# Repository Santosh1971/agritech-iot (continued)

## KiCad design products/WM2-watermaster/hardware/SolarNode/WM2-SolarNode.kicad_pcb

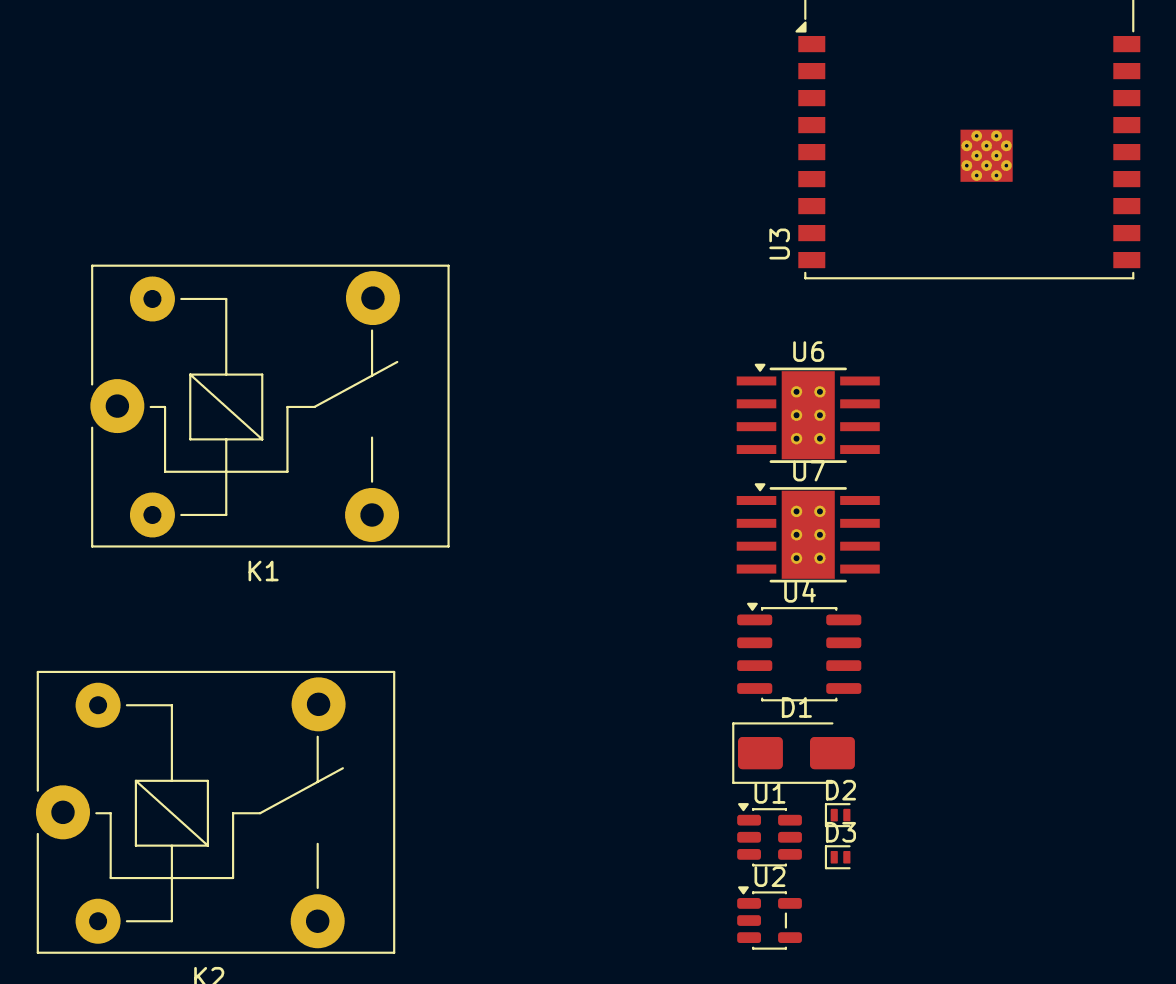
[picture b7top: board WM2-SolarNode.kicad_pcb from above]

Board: 2 copper layers, 11 parts (0 on the bottom side), 12 nets, no tracks yet.

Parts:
D1: SS34 (reverse-polarity); D_SMA
D2: PESD3V3U1UL (D-); D_SOD-882
D3: PESD3V3U1UL (D+); D_SOD-882
K1, K2: SRD-05VDC-SL-C; Relay_SPDT_SANYOU_SRD_Series_Form_C
U1: AP63205WU (fixed 5.0V out); TSOT-23-6
U2: AP2112K-3.3; SOT-23-5
U3: ESP32-C3-WROOM-02
U4: DS1307Z+; SOIC-8_3.9x4.9mm_P1.27mm
U6, U7: DRV8871DDA; Texas_HTSOP-8-1EP_3.9x4.9mm_P1.27mm_EP2.95x4.9mm_Mask2.4x3.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

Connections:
+3V3: U2.5 (VOUT), U3.1 (3V3), U4.8 (VCC)
+5V: K1.2, K2.2, U1.1 (FB), U2.1 (VIN), U2.3 (EN)
+12V: D1.1 (K), U1.2 (EN), U1.3 (IN), U6.5 (VM), U7.5 (VM)
/I2C_SCL: U3.8 (IO9), U4.6 (SCL)
/I2C_SDA: U3.7 (IO8), U4.5 (SDA)
/USB_DM: D2.2 (A), U3.13 (IO18)
/USB_DP: D3.2 (A), U3.14 (IO19)
/VALVE1_IN1: U3.10 (IO10), U6.3 (IN1)
/VALVE1_IN2: U3.11 (IO20/RXD), U6.2 (IN2)
/VALVE2_IN1: U3.12 (IO21/TXD), U7.3 (IN1)
/VALVE2_IN2: U3.16 (IO2), U7.2 (IN2)
GND: D2.1 (K), D3.1 (K), U1.4 (GND), U2.2 (GND), U3.9 (GND), U3.19 (GND), U4.4 (GND), U6.1 (GND), U6.7 (GND), U6.9 (GND), U7.1 (GND), U7.7 (GND), U7.9 (GND)

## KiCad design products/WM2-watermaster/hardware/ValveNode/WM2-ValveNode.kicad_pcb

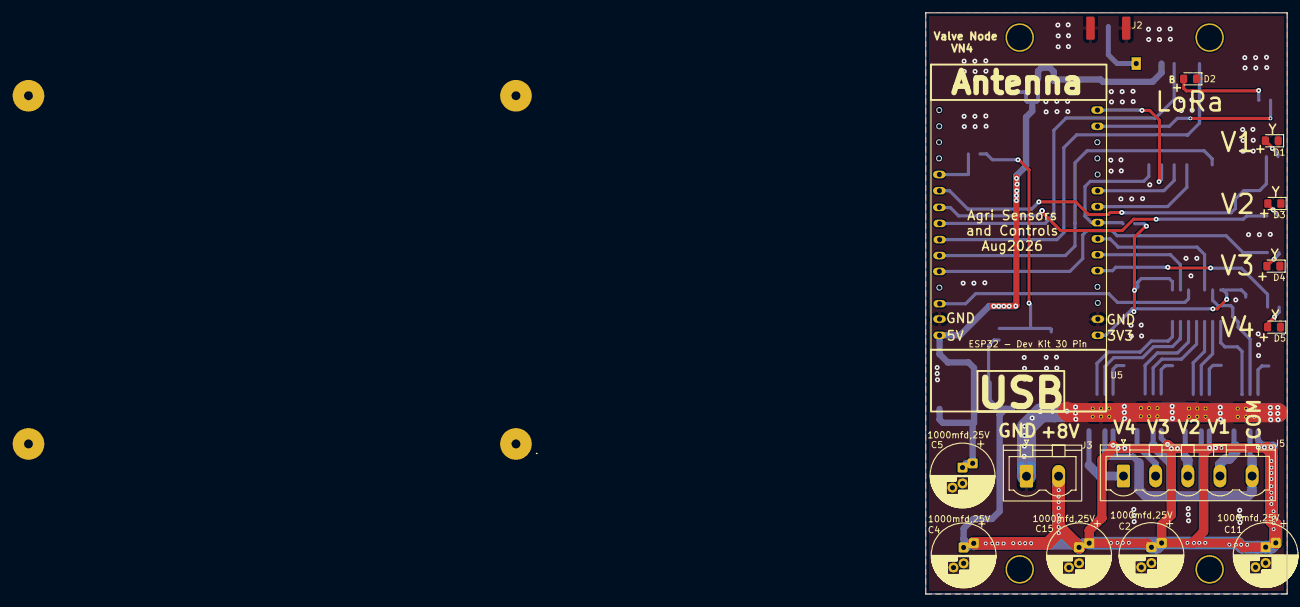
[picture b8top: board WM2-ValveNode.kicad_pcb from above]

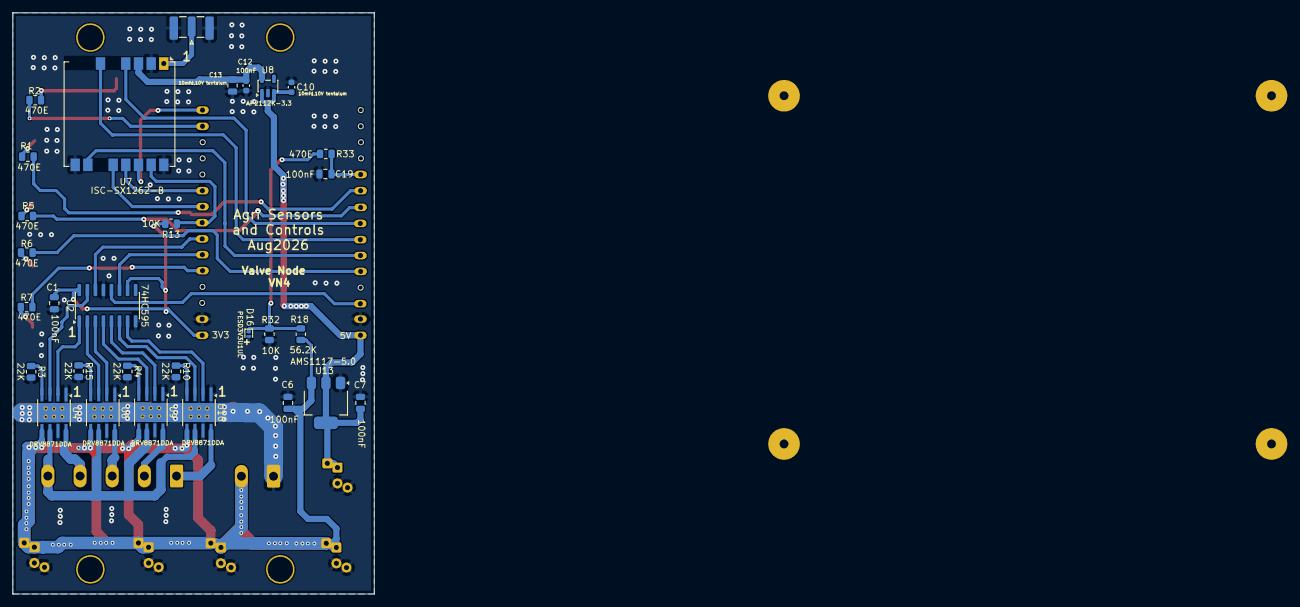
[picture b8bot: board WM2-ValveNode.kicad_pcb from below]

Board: 2 copper layers, 57.1 x 91.8 mm, 45 parts (30 on the bottom side), 45 nets.

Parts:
.: MountingHole; MountingHole_3.2mm_M3
C1, C6, C7, C13, C19: 100nF; C_0805_2012Metric
C2, C4, C5, C11, C15: 1000mfd,25V; CP_Radial_D10.0mm_P2.50mm_P5.00mm
C10, C12: 10mfd,10V tentalum; C_0603_1608Metric
D1: LED_V1_Yellow; LED_0805_2012Metric_Pad1.15x1.40mm_HandSolder
D2: LED_Blue_LoRa; LED_0805_2012Metric_Pad1.15x1.40mm_HandSolder
D3: LED_V2_Yellow; LED_0805_2012Metric_Pad1.15x1.40mm_HandSolder
D4: LED_V3_Yellow; LED_0805_2012Metric_Pad1.15x1.40mm_HandSolder
D5: LED_V4_Yellow; LED_0805_2012Metric_Pad1.15x1.40mm_HandSolder
D16: PESD3V3U1UL; D_SOD-882
H1: MountingHole; MountingHole_3.2mm_M3
J2: Conn_Coaxial_Small; SMA_Samtec_SMA-J-P-H-ST-EM1_EdgeMount
J3: PWR_CONN; PhoenixContact_MSTBVA_2,5_2-G-5,08_1x02_P5.08mm_Vertical
J5: Conn_01x05_Pin; PhoenixContact_MSTBVA_2,5_5-G-5,08_1x05_P5.08mm_Vertical
R1, R2, R5, R6, R7, R33: 470E; R_0805_2012Metric
R3, R4, R10, R15: 22K; R_0805_2012Metric
R13, R32: 10K; R_0805_2012Metric
R18: 56.2K; R_0805_2012Metric
U2: 74HC595; SOIC-16_3.9x9.9mm_P1.27mm
U4, U6, U9, U10: DRV8871DDA; Texas_HTSOP-8-1EP_3.9x4.9mm_P1.27mm_EP2.95x4.9mm_Mask2.4x3.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
U5: ESP32 30 Pin CP2102 Development Board; ESP32-C3-DevKitM-1
U7: ISC-SX1262-B; Ai-Thinker-Ra-01-LoRa
U8: AP2112K-3.3; SOT-23-5
U13: AMS1117-5.0; SOT-223-3_TabPin2

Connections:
+3.3V: C1.1, R13.1, U2.10 (~SRCLR), U2.16 (VCC), U5.1 (3V3_Out)
+3.3VL: C12.1, C13.1, U7.3 (VDD), U8.5 (VOUT)
+5V: C5.1, C7.1, C10.1, U5.30 (VIN/5V_Power_IN), U8.1 (VIN), U8.3 (EN), U13.2 (VO)
+8V: C2.1, C4.1, C6.1, C11.1, C15.1, J3.2, R18.1, U4.5 (VM), U6.5 (VM), U9.5 (VM), U10.5 (VM), U13.3 (VI)
/BUSY: U5.25 (D27), U7.10 (DIO4/BUSY)
/Batt_Mon: C19.1, R33.1, U5.20 (D35/Input_only)
/DIO1: U5.24 (D26), U7.6 (DIO1)
/LoRa_LED: R2.1, U5.14 (D22/I2C_SCL)
/MISO: U5.10 (D19), U7.13 (MISO)
/MOSI: U5.15 (D23), U7.14 (MOSI)
/NSS: R13.2, U5.8 (D5/BootSensitive), U7.15 (~NSS)
/RESET: U5.23 (D25), U7.4 (~RESET)
/SCK: U5.9 (D18), U7.12 (SCK)
/V1_IN1: U2.15 (QA), U4.3 (IN1)
/V1_IN2: U2.1 (QB), U4.2 (IN2)
/V1_LED: R1.1, U5.21 (D32)
/V1_OUT: J5.4, U4.8 (OUT2)
/V2_IN1: U2.2 (QC), U6.3 (IN1)
/V2_IN2: U2.3 (QD), U6.2 (IN2)
/V2_LED: R5.1, U5.22 (D33)
/V2_OUT: J5.3, U6.8 (OUT2)
/V3_IN1: U2.4 (QE), U9.3 (IN1)
/V3_IN2: U2.5 (QF), U9.2 (IN2)
/V3_LED: R6.1, U5.26 (D14)
/V3_OUT: J5.2, U9.8 (OUT2)
/V4_IN1: U2.6 (QG), U10.3 (IN1)
/V4_IN2: U2.7 (QH), U10.2 (IN2)
/V4_LED: R7.1, U5.5 (D4)
/V4_OUT: J5.1, U10.8 (OUT2)
/V_Com_OUT: J5.5, U4.6 (OUT1), U6.6 (OUT1), U9.6 (OUT1), U10.6 (OUT1)
/Valve_CLK: U2.11 (SRCLK), U5.6 (Rx2/D16)
/Valve_DATA: U2.14 (SER), U5.7 (Tx2/D17)
/Valve_LATCH: U2.12 (RCLK), U5.28 (D13)
GND: C1.2, C2.2, C4.2, C5.2, C6.2, C7.2, C10.2, C11.2, C12.2, C13.2, C15.2, C19.2, D1.1 (K), D2.1 (K), D3.1 (K), D4.1 (K), D5.1 (K), D16.2 (A), J2.2 (Ext), J3.1, R3.2, R4.2, R10.2, R15.2, R32.2, U2.8 (GND), U2.13 (~OE), U4.1 (GND), U4.7 (GND), U4.9 (GND), U5.2 (GND), U5.29 (GND), U6.1 (GND), U6.7 (GND), U6.9 (GND), U7.2 (GND), U7.9 (GND), U7.16 (GND), U8.2 (GND), U9.1 (GND), U9.7 (GND), U9.9 (GND), U10.1 (GND), U10.7 (GND), U10.9 (GND), U13.1 (GND)
unnamed: D1.2 (A), R1.2
unnamed: D2.2 (A), R2.2
unnamed: D3.2 (A), R5.2
unnamed: D4.2 (A), R6.2
unnamed: D5.2 (A), R7.2
unnamed: D16.1 (K), R18.2, R32.1, R33.2
unnamed: J2.1 (In), U7.1 (ANT)
unnamed: R3.1, U4.4 (ILIM)
unnamed: R15.1, U6.4 (ILIM)
unnamed: R4.1, U9.4 (ILIM)
unnamed: R10.1, U10.4 (ILIM)

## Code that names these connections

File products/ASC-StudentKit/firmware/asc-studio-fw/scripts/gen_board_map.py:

"""Pre-build: generate src/board_map.h from the kit pin map.

products/ASC-StudentKit/hardware/pinmap.json is the single source of truth for
which GPIO sits behind each port (check_pinmap.py checks it). This writes the
same table as C so the firmware can't drift from the hardware. Also runnable
by hand: `python3 scripts/gen_board_map.py`.
"""
import json
import os

try:
    Import("env")  # noqa: F821 -- provided by PlatformIO's SCons environment
    PROJECT = env["PROJECT_DIR"]  # noqa: F821
except NameError:
    PROJECT = os.path.dirname(os.path.dirname(os.path.abspath(__file__)))

PINMAP = os.path.normpath(os.path.join(PROJECT, "../../hardware/pinmap.json"))
OUT = os.path.join(PROJECT, "src", "board_map.h")

with open(PINMAP) as f:
    pm = json.load(f)


def gpio(board, signal):
    for g, s in board["pins"].items():
        if s == signal:
            return int(g)
    return -1


def board_struct(key):
    b = pm["boards"][key]
    s = [gpio(b, f"S{i}") for i in range(1, 9)]
    o = [gpio(b, f"OUT{i}") for i in range(1, 5)]
    fields = {
        "sensorPorts": b["sensor_ports"], "i2cPorts": b["i2c_ports"], "relays": b["relays"],
        "i2cExtSda": gpio(b, "I2C_EXT_SDA"), "i2cExtScl": gpio(b, "I2C_EXT_SCL"),
        "i2cIntSda": gpio(b, "I2C_INT_SDA"), "i2cIntScl": gpio(b, "I2C_INT_SCL"),
        "led": gpio(b, "LED"), "buzzer": gpio(b, "BUZZER"), "pairBtn": gpio(b, "PAIR_BTN"),
        "rtcInt": gpio(b, "RTC_INT"), "vinSense": gpio(b, "VIN_SENSE"), "vbatAdc": gpio(b, "VBAT_ADC"),
        "vbatEn": gpio(b, "VBAT_EN"), "valve": gpio(b, "VALVE"),
    }
    body = ", ".join(f".{k} = {v}" for k, v in fields.items())
    return (f'  {{ .name = "{key}", .sensor = {{{", ".join(map(str, s))}}}, '
            f'.out = {{{", ".join(map(str, o))}}}, {body} }}')


ids = pm["board_id"]
text = f"""// GENERATED by scripts/gen_board_map.py from hardware/pinmap.json. Do not edit.
#pragma once
#include <stdint.h>

struct BoardMap {{
  const char* name;
  int8_t sensor[8];  // S1..S8, -1 = not on this board
  int8_t out[4];     // OUT1..OUT4
  uint8_t sensorPorts, i2cPorts, relays;
  int8_t i2cExtSda, i2cExtScl, i2cIntSda, i2cIntScl;
  int8_t led, buzzer, pairBtn, rtcInt, vinSense, vbatAdc, vbatEn, valve;
}};

static const BoardMap BOARDS[] = {{
{board_struct("mini")},
{board_struct("mega")},
}};

// BOARD_ID divider ratios (fraction of 3V3) and the pin they are read on.
static const int8_t BOARD_ID_PIN = {gpio(pm["boards"]["mini"], "BOARD_ID")};
static const float BOARD_ID_MINI = {ids["mini"]}f;
static const float BOARD_ID_MEGA = {ids["mega"]}f;
"""

old = open(OUT).read() if os.path.exists(OUT) else ""
if old != text:
    with open(OUT, "w") as f:
        f.write(text)
    print(f"[gen_board_map] wrote {OUT}")

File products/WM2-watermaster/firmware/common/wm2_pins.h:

#pragma once
// WM2-WaterMaster pin map (ESP32-WROOM-32D, U4).
// Source of truth: hardware/WaterMaster/WM2-WaterMaster.kicad_sch
// (extracted from the KiCad netlist, 2026-10-24). Shared by selftest and
// the main firmware -- change it here only if the schematic changes.

#include <stdint.h>

namespace wm2 {

// --- Sensor inputs (input-only pins, 10K pull-up to 3.3V on board,
//     470R series + 100pF to GND). Idle with nothing plugged in = HIGH.
// Index = the FL number printed on the board. The PCB places J4 (wired to
// Flow_MCU4 = IO39) under the "FL3" silkscreen, next to LD5, and J3 (IO36)
// under "FL4", next to LD6; reading IO39 as flow 3 and IO36 as flow 4 makes
// connector label, LED and app agree (WM2 rev A, found 2026-11-18).
constexpr uint8_t PIN_FLOW[4] = {34, 35, 39, 36};  // FL1 J2, FL2 J5, FL3 J4, FL4 J3
constexpr uint8_t PIN_PS      = 32;                // J1 pressure switch, closes to GND (active LOW)

// --- Indicator LEDs (active HIGH, 470R). LD1 power LED is hardwired to +12V.
constexpr uint8_t PIN_LED_FLOW[4] = {25, 26, 19, 18};  // LD3..LD6
constexpr uint8_t PIN_LED_PS      = 27;                // LD7
constexpr uint8_t PIN_LED_WIFI    = 14;                // LD2 (blue)

// --- Latching-valve drivers, DRV8871 (U1 = V1/J7, U2 = V2/J8).
//     IN1=H IN2=L -> OUT1 high (forward) | IN1=L IN2=H -> reverse
//     both LOW -> coast, chip sleeps after ~1ms. Never leave both HIGH (brake).
//     ILIM 22K -> ~2.9A. VM comes from +12V_LV (solar/battery), not from USB 5V.
//     Direction LEDs across each output pair: Green / Yellow (LD8-LD11).
constexpr uint8_t PIN_V1_IN1 = 13;
constexpr uint8_t PIN_V1_IN2 = 4;
constexpr uint8_t PIN_V2_IN1 = 16;
constexpr uint8_t PIN_V2_IN2 = 17;

// --- Battery / solar 12V monitor: +12V -> 56.2K -> node -> 10K -> GND,
//     node -> 470R -> IO33 (100nF filter).
constexpr uint8_t PIN_BATT_ADC = 33;
constexpr float   BATT_DIVIDER = (56.2f + 10.0f) / 10.0f;  // 6.62

// --- DS1307Z+ RTC (U5, VCC 5V, CR2032 backup), 4K7 pull-ups to 3.3V.
constexpr uint8_t PIN_SDA = 21;
constexpr uint8_t PIN_SCL = 22;
constexpr uint8_t RTC_I2C_ADDR = 0x68;

// Unconnected / free: IO2, IO5, IO12, IO15, IO23 (IO2/5/12/15 are strapping pins).

}  // namespace wm2

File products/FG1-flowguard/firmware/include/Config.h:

#pragma once

// ---------- Device ----------
#define DEVICE_ID           "SWC_001"
// CI overrides this via scripts/inject_firmware_version.py (FIRMWARE_VERSION_OVERRIDE
// env var, set to dev-<shortsha> for auto-builds) — bump this by hand to match
// whenever cutting an actual dashboard release, e.g. "1.1.0".
#ifndef FIRMWARE_VERSION
#define FIRMWARE_VERSION    "1.3.4"
#endif

// ---------- BLE ----------
#define BLE_DEVICE_NAME     "SmartWaterCtrl"
#define BLE_SERVICE_UUID        "12345678-1234-1234-1234-123456789abc"
#define BLE_CHAR_RX_UUID        "12345678-1234-1234-1234-123456789abd"
#define BLE_CHAR_TX_UUID        "12345678-1234-1234-1234-123456789abe"

// ---------- MQTT ----------
#define MQTT_BROKER         "mqtt.agrisenseandcontrol.in"
#define MQTT_PORT           1883
#define MQTT_USER           "fg1-device"
#define MQTT_PASS           "asacfg1"
// Topics are now built at runtime in MQTTClient.cpp from the actual
// per-device ID (see computeDeviceId() in main.cpp) — these used to be
// fixed here at compile time as "swc/SWC_001/...", which every physical
// device shared identically, a real collision risk with more than one
// unit in Cloud mode at once.
// ---------- WiFi fallback (SoftAP, no field WiFi available) ----------
#define SOFTAP_SSID             DEVICE_ID
#define SOFTAP_PASSWORD         "water1234"  // TODO: derive per-device password for production
#define WIFI_CONNECT_TIMEOUT_MS 15000        // boot-time connect attempt
#define WIFI_RETRY_INTERVAL_MS  60000        // background retry while in fallback

// ---------- OTA (bench SoftAP flash + WiFi flash from the app) ----------
// Gates /update (ElegantOTA's own portal + upload endpoint) so that once a
// device is reachable over a customer's home WiFi (Cloud mode), anyone else
// on that same network can't reflash it — reachable-but-unauthenticated was
// an acceptable bench tradeoff on an isolated SoftAP with a developer
// physically present; it stopped being one the moment WiFi OTA started
// working over STA. Must match WifiOtaFlasher.kt's OTA_USERNAME/PASSWORD on
// the app side — same TODO as SOFTAP_PASSWORD above about deriving this
// per-device before this ships to a dealer network.
#define OTA_USERNAME            "nbagri"
#define OTA_PASSWORD            "flash-nb-2026"

// ---------- GPIO ----------
// Pin assignments per current FG1 schematic (ESP32-30pin dev kit sheet).
#define RELAY_PIN           19    // D19 — RELAY1_MCU (relay driver input via ULN2003)
// No separate relay/pump LED GPIO exists on this board — LED_YELLOW_PUMP is
// wired on the ULN2003 driver's output side (next to the relay coil), so it
// lights automatically whenever the relay fires. RelayControl.begin() is
// called with no LED pin (defaults to 255 = "no LED wired").
#define FLOW_SENSOR_PIN     35    // D35 — FLOW1_MCU (input-only pin; flow pulse input)
#define FLOW_SENSOR_LED_PIN 32    // D32 — FLOW1_LED_MCU (flow sensor status LED)
#define WIFI_LED_PIN        2     // D2/OnBoardLED — doubles as WiFi + power status LED
#define I2C_SDA             21    // D21/I2C_SDA
#define I2C_SCL             22    // D22/I2C_SCL

// ---------- Flow Sensor ----------
#define DEFAULT_PULSES_PER_LITER  450

// ---------- Scheduler ----------
#define MAX_CYCLES          4
#define NVS_NAMESPACE       "swc"
// Packed into a single NVS blob (~sizeof(HistoryEntry) * this many bytes,
// roughly 68 bytes/entry). NVS partition here is only ~20KB total shared
// with cycles/WiFi/MQTT/running-state, and NVS itself needs headroom
// beyond the partition's nominal size for its own page/wear-leveling
// bookkeeping — 200 entries (~13KB) left too little margin and caused
// real "NOT_ENOUGH_SPACE" failures in testing. 60 entries (~4KB) leaves
// comfortable room; still ~12 days of history at 5 events/day.
#define HISTORY_MAX_ENTRIES 60   // ~12 days at moderate use (5 events/day)

// ---------- Timing ----------
#define STATUS_PUBLISH_INTERVAL_MS   5000
#define SCHEDULE_CHECK_INTERVAL_MS   1000
#define STATE_SAVE_INTERVAL_MS       10000

// ---------- LED Blink Patterns ----------
// WiFi LED
#define WIFI_LED_CONNECTING_ON_MS    200   // fast blink = connecting
#define WIFI_LED_CONNECTING_OFF_MS   200
#define WIFI_LED_CONNECTED_ON_MS     1000  // slow blink = connected, no MQTT
#define WIFI_LED_CONNECTED_OFF_MS    1000
#define WIFI_LED_MQTT_ON_MS          50    // double blink = WiFi + MQTT ok
#define WIFI_LED_MQTT_OFF_MS         50

// Flow LED
#define FLOW_LED_PULSE_MS            50    // brief flash per pulse burst

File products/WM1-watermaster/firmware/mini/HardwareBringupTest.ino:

// Water Manager-Mini — Hardware Bring-Up Diagnostic
//
// One sketch to flash for initial testing of the real 6-relay PCB,
// BEFORE wiring up the full RelayController/IrrigationController/
// Scheduler stack. Open Serial Monitor at 115200 baud, use the menu.
//
// Pin map per the spec (GPIO numbers, not dev-kit pin numbers):
//   Flow      : GPIO36 (VP)  — interrupt, pulse count
//   Press1    : GPIO39 (VN)  — ADC
//   Press2    : GPIO34       — ADC
//   Batt_Mon  : GPIO35       — ADC
//   IN2       : GPIO32       — ADC
//   IN3       : GPIO33       — ADC
//   IN1       : GPIO14       — digital, pulled up (HIGH=power OK, LOW=no power)
//   RLY_DATA  : GPIO17
//   RLY_CLK   : GPIO16
//   RLY_LATCH : GPIO13
//   RTC (DS1307) : I2C, SDA=GPIO21, SCL=GPIO22, address 0x68

#include <Arduino.h>
#include <Wire.h>

#define PIN_FLOW      36
#define PIN_PRESS1    39
#define PIN_PRESS2    34
#define PIN_BATT      35
#define PIN_IN2       32
#define PIN_IN3       33
#define PIN_IN1       14
#define PIN_RLY_DATA  17
#define PIN_RLY_CLK   16
#define PIN_RLY_LATCH 13
#define DS1307_ADDR   0x68

volatile uint32_t flowPulseCount = 0;
void IRAM_ATTR onFlowPulse() { flowPulseCount++; }

uint8_t relayState = 0;  // bit N = relay N (0=RL1/pump ... 5=RL6)

void pushRelayState() {
  digitalWrite(PIN_RLY_LATCH, LOW);
  shiftOut(PIN_RLY_DATA, PIN_RLY_CLK, MSBFIRST, relayState);
  digitalWrite(PIN_RLY_LATCH, HIGH);
}

void setRelay(uint8_t index, bool on) {
  if (index > 5) return;
  if (on) relayState |= (1 << index); else relayState &= ~(1 << index);
  pushRelayState();
}

// --- Raw DS1307 read/write (BCD), no external RTC library needed ---
uint8_t bcd2dec(uint8_t v) { return ((v / 16) * 10) + (v % 16); }
uint8_t dec2bcd(uint8_t v) { return ((v / 10) * 16) + (v % 10); }

bool ds1307Read(uint8_t &h, uint8_t &m, uint8_t &s) {
  Wire.beginTransmission(DS1307_ADDR);
  Wire.write(0x00);
  if (Wire.endTransmission() != 0) return false;
  Wire.requestFrom(DS1307_ADDR, 3);
  if (Wire.available() < 3) return false;
  s = bcd2dec(Wire.read() & 0x7F);
  m = bcd2dec(Wire.read());
  h = bcd2dec(Wire.read() & 0x3F);
  return true;
}

void ds1307Set(uint8_t h, uint8_t m, uint8_t s) {
  Wire.beginTransmission(DS1307_ADDR);
  Wire.write(0x00);
  Wire.write(dec2bcd(s));
  Wire.write(dec2bcd(m));
  Wire.write(dec2bcd(h));
  Wire.endTransmission();
}

void i2cScan() {
  Serial.println("Scanning I2C bus...");
  bool found = false;
  for (uint8_t addr = 1; addr < 127; addr++) {
    Wire.beginTransmission(addr);
    if (Wire.endTransmission() == 0) {
      Serial.printf("  Found device at 0x%02X%s\n", addr,
                    addr == DS1307_ADDR ? "  <-- DS1307 RTC" : "");
      found = true;
    }
  }
  if (!found) Serial.println("  Nothing found — check SDA/SCL wiring.");
}

void testRelaysSequential() {
  Serial.println("Cycling relays 1-6 one at a time (2s each)...");
  for (uint8_t i = 0; i < 6; i++) {
    Serial.printf("  RL%u ON\n", i + 1);
    setRelay(i, true);
    delay(2000);
    setRelay(i, false);
    delay(300);
  }
  Serial.println("Done. All relays should now be off.");
}

void readPressureRaw(const char* label, uint8_t pin) {
  int raw = analogRead(pin);
  float volts = raw * (3.3f / 4095.0f);
  Serial.printf("  %s: raw=%d  volts=%.3f\n", label, raw, volts);
}

void printMenu() {
  Serial.println();
  Serial.println("--- Water Manager-Mini Bring-Up Menu ---");
  Serial.println("i - I2C scan (confirm DS1307 at 0x68)");
  Serial.println("t - Read RTC time");
  Serial.println("T - Set RTC time to compile time (once, then use 't' to confirm)");
  Serial.println("r - Cycle all 6 relays sequentially");
  Serial.println("1-6 - Toggle a single relay by number");
  Serial.println("f - Show flow pulse count (5s window)");
  Serial.println("p - Show pressure sensor 1/2 raw + voltage");
  Serial.println("b - Show battery monitor raw + voltage");
  Serial.println("n - Show IN1 (No Power) state");
  Serial.println("x - Show IN2/IN3 raw + voltage");
  Serial.println("a - Run full diagnostic (everything once)");
  Serial.println("-----------------------------------------");
}

void runFullDiagnostic() {
  i2cScan();
  uint8_t h, m, s;
  if (ds1307Read(h, m, s)) Serial.printf("RTC time: %02u:%02u:%02u\n", h, m, s);
  else Serial.println("RTC read FAILED");

  Serial.println("Pressure sensors:");
  readPressureRaw("Press1", PIN_PRESS1);
  readPressureRaw("Press2", PIN_PRESS2);
  Serial.println("Battery:");
  readPressureRaw("Batt_Mon", PIN_BATT);
  Serial.println("IN2/IN3:");
  readPressureRaw("IN2", PIN_IN2);
  readPressureRaw("IN3", PIN_IN3);
  Serial.printf("IN1 (No Power sense): %s (%s)\n",
                digitalRead(PIN_IN1) ? "HIGH" : "LOW",
                digitalRead(PIN_IN1) ? "power OK" : "NO POWER");
  Serial.printf("Flow pulses so far: %u\n", flowPulseCount);
}

void setup() {
  Serial.begin(115200);
  delay(500);

  pinMode(PIN_RLY_DATA, OUTPUT);
  pinMode(PIN_RLY_CLK, OUTPUT);
  pinMode(PIN_RLY_LATCH, OUTPUT);
  pushRelayState();  // all relays off at boot — fail-safe

  pinMode(PIN_IN1, INPUT);  // externally pulled up per schematic
  pinMode(PIN_FLOW, INPUT);
  attachInterrupt(digitalPinToInterrupt(PIN_FLOW), onFlowPulse, RISING);

  Wire.begin(21, 22);  // SDA, SCL

  printMenu();
}

void loop() {
  if (!Serial.available()) { delay(20); return; }
  char c = Serial.read();

  switch (c) {
    case 'i': i2cScan(); break;
    case 't': {
      uint8_t h, m, s;
      if (ds1307Read(h, m, s)) Serial.printf("RTC time: %02u:%02u:%02u\n", h, m, s);
      else Serial.println("RTC read FAILED — check wiring/I2C scan first");
      break;
    }
    case 'T': {
      // Sets to a fixed placeholder time — replace with real time as needed.
      ds1307Set(12, 0, 0);
      Serial.println("RTC set to 12:00:00 (placeholder) — press 't' to confirm.");
      break;
    }
    case 'r': testRelaysSequential(); break;
    case '1': case '2': case '3': case '4': case '5': case '6': {
      uint8_t idx = c - '1';
      bool newState = !((relayState >> idx) & 1);
      setRelay(idx, newState);
      Serial.printf("RL%u -> %s\n", idx + 1, newState ? "ON" : "OFF");
      break;
    }
    case 'f': {
      flowPulseCount = 0;
      Serial.println("Counting flow pulses for 5s...");
      delay(5000);
      Serial.printf("  Pulses: %u\n", flowPulseCount);
      break;
    }
    case 'p':
      readPressureRaw("Press1", PIN_PRESS1);
      readPressureRaw("Press2", PIN_PRESS2);
      break;
    case 'b': readPressureRaw("Batt_Mon", PIN_BATT); break;
    case 'n':
      Serial.printf("IN1: %s (%s)\n", digitalRead(PIN_IN1) ? "HIGH" : "LOW",
                    digitalRead(PIN_IN1) ? "power OK" : "NO POWER");
      break;
    case 'x':
      readPressureRaw("IN2", PIN_IN2);
      readPressureRaw("IN3", PIN_IN3);
      break;
    case 'a': runFullDiagnostic(); break;
    default: printMenu(); break;
  }
}
